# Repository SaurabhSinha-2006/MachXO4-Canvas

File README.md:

# MachXO4-Canvas

**MachXO4-Canvas** is a flexible, beginner-friendly FPGA development board designed specifically for educational use and DIY assembly. Built on a standard 100x100mm 2-layer PCB, this board eliminates standard manufacturing and assembly bottlenecks by utilizing robust, easy-to-solder components, including a massive through-hole USB-A female connector. 

With zero Design Rule Check (DRC) errors, this layout is highly optimized for standard 2-layer board house constraints.

## Repository Structure

Based on the project organization, here is where to find all relevant design and production files:

*   **[`/Doc`](Doc/)**[cite: 3]
    *   [`machx04_devboard.png`](Doc/machx04_devboard.png) - High-resolution 3D render of the final board[cite: 3].
    *   [`machx04_devboard.pdf`](Doc/machx04_devboard.pdf) - The complete system schematic[cite: 3].
    *   [`layout_final.pdf`](Doc/layout_final.pdf) - High-resolution 2D PCB layout for visual routing inspection[cite: 3].
*   **[`/Fabrication`](Fabrication/)**[cite: 3]
    *   [`machx04_gerber_files.zip`](Fabrication/machx04_gerber_files.zip) - The final, production-ready Gerber and Drill files[cite: 3].
*   **[`/Hardware`](Hardware/)**[cite: 3]
    *   Contains the native KiCad 8 source files (`.kicad_pro`, `.kicad_sch`, `.kicad_pcb`) and the `/Custom Library` folder for component footprints and symbols[cite: 3].

## Hardware Specifications

*   **Core Processor:** MachXO4 FPGA paired with a dedicated configuration EEPROM.
*   **Programming Interface:** Onboard FTDI JTAG/UART bridge for seamless flashing and serial communication directly over USB.
*   **Power Architecture:** 5V to 3.3V and 1.8V low-dropout (LDO) regulators with optimized thermal copper pours.
*   **User I/O:** Programmable onboard LEDs, tactile user switches, and a dedicated hardware system reset.
*   **Form Factor & Connectivity:** 100x100mm Edge.Cuts with a robust, 4-pin female USB-A interface, entirely removing the microscopic drill constraints of standard USB-C ports.

## Fabrication & Manufacturing

This board is fully validated for standard, low-cost 2-layer manufacturing. 
To manufacture this board, simply provide the factory with the **[Gerber Release ZIP](Fabrication/machx04_gerber_files.zip)**[cite: 3]. 

If your fabrication engineer requires a visual preview before running the job, you can share the **[2D Layout PDF](Doc/layout_final.pdf)**[cite: 3] and the **[System Schematic](Doc/machx04_devboard.pdf)**[cite: 3].

## Modifying the Design

To open and modify this project:
1. Clone this repository to your local machine.
2. Ensure you have KiCad installed.
3. Navigate to the `Hardware/` directory and open `machx04_devboard.kicad_pro`[cite: 3].
4. The project utilizes localized parts in the `Hardware/Custom Library/` folder, which should link automatically upon opening[cite: 3].

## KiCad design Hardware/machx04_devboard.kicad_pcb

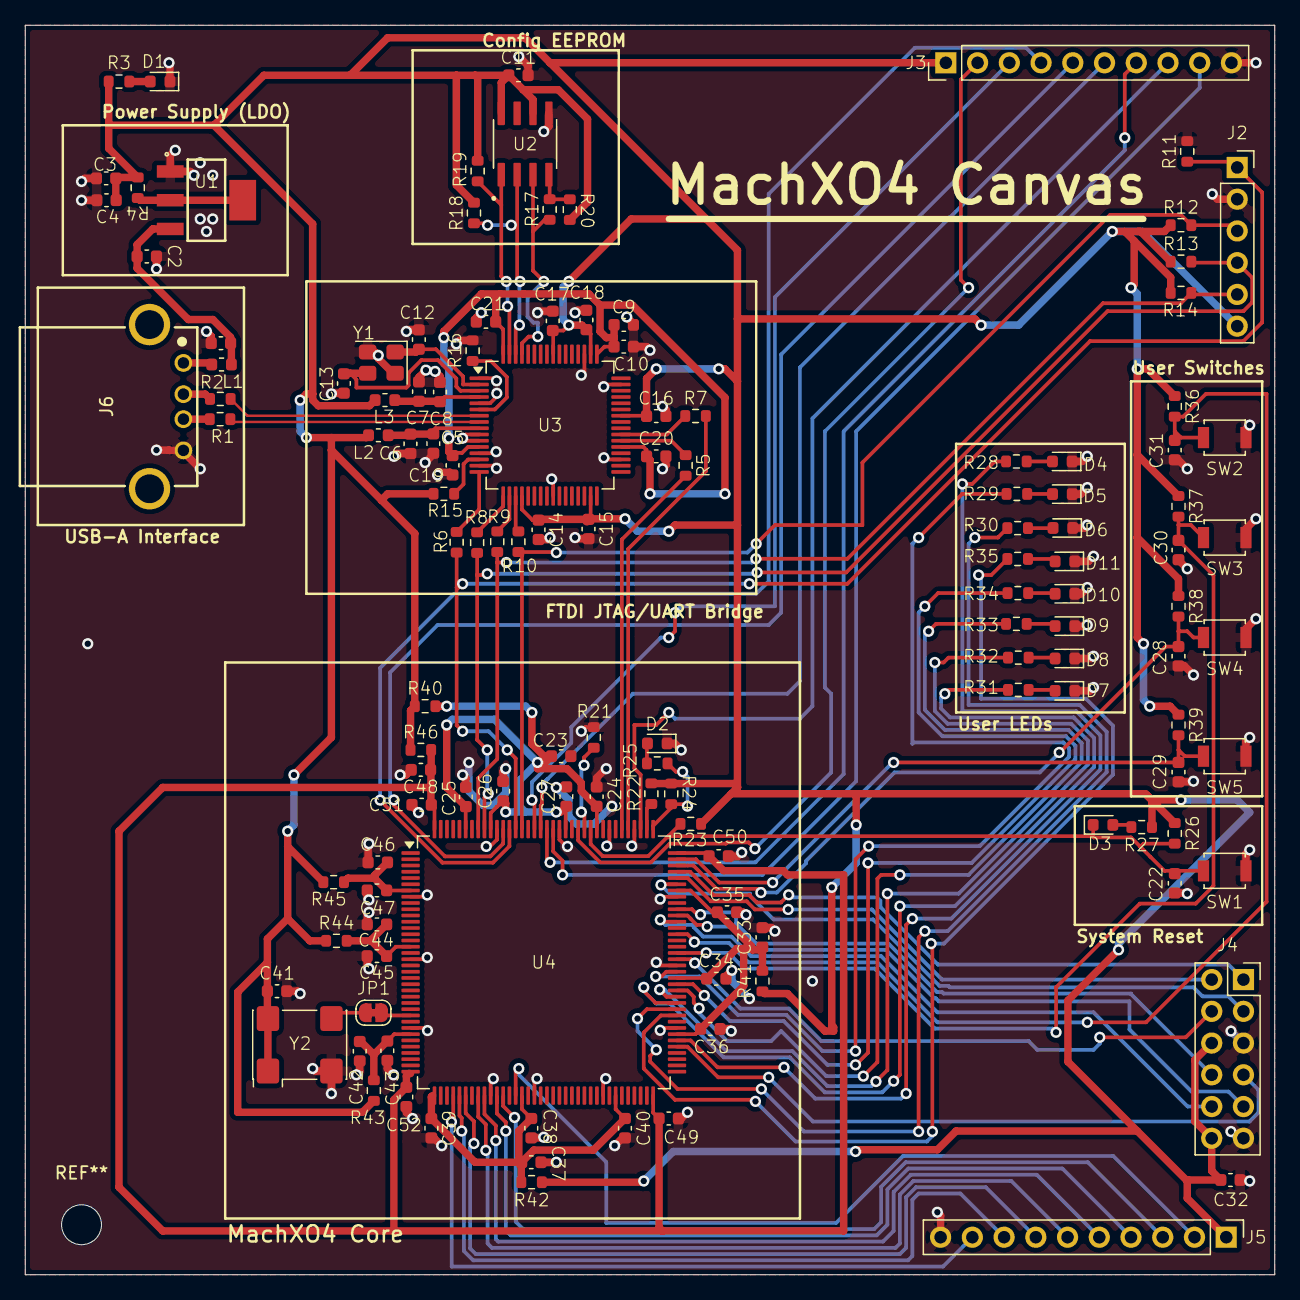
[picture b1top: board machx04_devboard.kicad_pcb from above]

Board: 2 copper layers, 100.0 x 100.0 mm, 129 parts (0 on the bottom side), 92 nets.

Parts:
C1, C4, C5, C8, C10, C11, C14, C15, C16, C17, C18, C19, C20, C21, C22, C24, C25, C26, C27, C28, C29, C30, C31, C32, C34, C35, C36, C38, C39, C40, C41, C43, C45, C47, C49, C50, C51, C52: 0.1uf; C_0603_1608Metric
C2, C9, C23, C33, C37, C42, C44, C46, C48: 10uf; C_0603_1608Metric
C3: 22uf; C_0603_1608Metric
C6, C7: 4.7uf; C_0603_1608Metric
C12, C13: 18pf; C_0603_1608Metric
D1, D2, D3, D4, D5, D6, D7, D8, D9, D10, D11: LED; LED_0603_1608Metric
J2: Conn_01x06_Socket; PinSocket_1x06_P2.54mm_Vertical
J3, J5: Conn_01x10_Socket; PinHeader_1x10_P2.54mm_Vertical
J4: Conn_02x06_Top_Bottom; PinSocket_2x06_P2.54mm_Vertical
J6: USB_A; 61400416021
JP1: Jumper_2_Open; SolderJumper-2_P1.3mm_Bridged_RoundedPad1.0x1.5mm
L1, L2, L3: 600ohm 500mA; L_0603_1608Metric
R1, R2, R4, R5, R6, R7, R8, R9, R10: 0; R_0603_1608Metric
R3, R25, R27, R28, R29, R30, R31, R32, R33, R34, R35: 1k; R_0603_1608Metric
R11, R15, R17: 2.2k; R_0603_1608Metric
R12, R13, R14, R26, R36, R37, R38, R39: 4.7k; R_0603_1608Metric
R16: 12k; R_0603_1608Metric
R18, R19, R20, R21, R22, R23, R24: 10k; R_0603_1608Metric
R40, R41, R42, R43, R44, R45, R46: 1; R_0603_1608Metric
SW1, SW2, SW3, SW4, SW5: SW_Push; SW_SPST_B3U-1000P
U1: NCP1117ST33T3G; SOT230P700X180-4N
U2: 93LC56C-I_SN; SOIC127P600X175-8N
U3: FT2232HL; LQFP-64_10x10mm_P0.5mm
U4: MachXO4_TQFP144; TQFP-144_20x20mm_P0.5mm
Y1: Crystal_GND24; Crystal_SMD_3225-4Pin_3.2x2.5mm
Y2: SG-8002CA; Oscillator_SMD_SeikoEpson_SG8002CA-4Pin_7.0x5.0mm

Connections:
+3.3V: C3.1, C4.1, C11.1, C14.1, C15.1, C16.1, C17.1, C18.1, C32.1, C41.1, J2.6, J3.1, J4.6, J4.12, J5.1, L2.1, L3.1, R3.1, R4.2, R12.1, R13.1, R14.1, R15.1, R18.1, R19.1, R20.1, R22.1, R23.1, R24.1, R26.1, R27.1, R36.1, R37.1, R38.1, R39.1, R40.1, R41.1, R42.1, R43.1, R44.1, R45.1, R46.1, U2.6 (ORG), U2.8 (VCC), U3.20 (VCCIO), U3.31 (VCCIO), U3.42 (VCCIO), U3.50 (VREGIN), U3.56 (VCCIO), Y2.1 (OE), Y2.4 (Vcc)
/bank0/EXP_HEADER1: J3.2, U4.121 (PT21B)
/bank0/EXP_HEADER2: J3.3, U4.128 (PT18A)
/bank0/EXP_HEADER3: J3.4, U4.132 (PT14B)
/bank0/EXP_HEADER4: J3.5, U4.133 (PT14A)
/bank0/EXP_HEADER5: J3.6, U4.127 (PT18B)
/bank0/EXP_HEADER6: J3.7, U4.126 (PT20C)
/bank0/EXP_HEADER7: J3.8, U4.111 (PT27B)
/bank0/EXP_HEADER8: J3.9, U4.125 (PT20D)
/bank1/LED1: R28.1, U4.78 (PR16A)
/bank1/LED2: R29.1, U4.89 (PR10C)
/bank1/LED3: R30.1, U4.83 (PR14B)
/bank1/LED4: R31.1, U4.84 (PR14A)
/bank1/LED5: R32.1, U4.85 (PR13B)
/bank1/LED6: R33.1, U4.86 (PR13A)
/bank1/LED7: R34.1, U4.87 (PR10D)
/bank1/LED8: R35.1, U4.82 (PR15A)
/bank1/PB1: C31.1, R36.2, SW2.2, U4.95 (PR8B)
/bank1/PB2: C30.1, R37.2, SW3.2, U4.92 (PR10A)
/bank1/PB3: C29.1, R39.2, SW5.2, U4.107 (PR2A)
/bank1/PB4: C28.1, R38.2, SW4.2, U4.106 (PR2B)
/bank1/PM1: J4.1, U4.105 (PR3A)
/bank1/PM2: J4.2, U4.104 (PR3B)
/bank1/PM3: J4.3, U4.103 (PR4C)
/bank1/PM4: J4.4, U4.91 (PR10B)
/bank1/PM5: J4.7, U4.77 (PR16B)
/bank1/PM6: J4.8, U4.99 (PR5B)
/bank1/PM7: J4.9, U4.98 (PR6A)
/bank1/PM8: J4.10, U4.97 (PR6B)
/bank2/EXP_HEAD9: J5.2, U4.50 (PB13B)
/bank2/EXP_HEAD10: J5.3, U4.48 (PB10B)
/bank2/EXP_HEAD11: J5.4, U4.47 (PB10A)
/bank2/EXP_HEAD12: J5.5, U4.45 (PB9B)
/bank2/EXP_HEAD13: J5.6, U4.44 (PB9A)
/bank2/EXP_HEAD14: J5.7, U4.42 (PB7A)
/bank2/EXP_HEAD15: J5.8, U4.41 (PB4B)
/bank2/EXP_HEAD16: J5.9, U4.40 (PB4A)
GND: C1.2, C2.2, C3.2, C4.2, C5.2, C6.2, C7.2, C8.2, C9.2, C10.2, C11.2, C12.2, C13.2, C14.2, C15.2, C16.2, C17.2, C18.2, C19.2, C20.2, C21.2, C22.2, C23.2, C24.2, C25.2, C26.2, C27.2, C28.2, C29.2, C30.2, C31.2, C32.2, C33.2, C34.2, C35.2, C36.2, C37.2, C38.2, C39.2, C40.2, C41.2, C42.1, C43.1, C44.1, C45.1, C46.1, C47.1, C48.2, C49.2, C50.2, C51.2, C52.2, D1.1 (K), D2.1 (K), D4.1 (K), D5.1 (K), D6.1 (K), D7.1 (K), D8.1 (K), D9.1 (K), D10.1 (K), D11.1 (K), J2.2, J3.10, J4.5, J4.11, J5.10, J6.4 (GND), R11.2, R16.1, R21.2, SW1.1, SW2.1, SW3.1, SW4.1, SW5.1, U1.1 (GND), U2.5 (VSS), U3.1 (GND), U3.5 (GND), U3.10 (AGND), U3.11 (GND), U3.13 (TEST), U3.15 (GND), U3.25 (GND), U3.35 (GND), U3.47 (GND), U3.51 (GND), U4.8 (GND), U4.18 (GND), U4.29 (GND), U4.46 (GND), U4.53 (GND), U4.64 (GND), U4.80 (GND), U4.90 (GND), U4.101 (GND), U4.112 (GND), U4.116 (GND), U4.124 (GND), U4.134 (GND), Y1.2 (G), Y1.4 (G), Y2.2 (GND)
unnamed: D1.2 (A), R3.2
unnamed: D2.2 (A), R25.2
unnamed: D3.2 (A), R27.2
unnamed: D4.2 (A), R28.2
unnamed: D5.2 (A), R29.2
unnamed: D6.2 (A), R30.2
unnamed: D7.2 (A), R31.2
unnamed: D8.2 (A), R32.2
unnamed: D9.2 (A), R33.2
unnamed: D10.2 (A), R34.2
unnamed: D11.2 (A), R35.2
unnamed: J6.3 (D+), R1.1
unnamed: J6.2 (D-), R2.1
unnamed: J6.1 (VBUS), L1.2
unnamed: JP1.1 (A), U4.27 (PL17A)
unnamed: JP1.2 (B), Y2.3 (OUT)
unnamed: R4.1, U1.2 (OUT), U1.4 (OUT)
unnamed: R18.2, U2.2 (CLK), U3.62 (EECLK)
unnamed: R19.2, U2.1 (CS), U3.63 (EECS)
unnamed: R17.2, U2.3 (DI), U3.61 (EEDATA)
unnamed: R17.1, R20.2, U2.4 (DO)
unnamed: R6.1, U3.16 (ADBUS0)
unnamed: R8.1, U3.17 (ADBUS1)
unnamed: R9.1, U3.18 (ADBUS2)
unnamed: R10.1, U3.19 (ADBUS3)
unnamed: R5.1, U3.38 (BDBUS0)
unnamed: R7.1, U3.39 (BDBUS1)
unnamed: C12.1, U3.2 (OSCI), Y1.1
unnamed: C13.1, U3.3 (OSCO), Y1.3
unnamed: R16.2, U3.6 (REF)
unnamed: C7.1, C8.1, L3.2, U3.4 (VPHY)
unnamed: C5.1, C6.1, L2.2, U3.9 (VPLL)
unnamed: R15.2, U3.14 (~RESET)
unnamed: R21.1, U4.120 (PT23C)
unnamed: R22.2, U4.110 (PT28C)
unnamed: R24.2, R25.1, U4.109 (PT28D)
PROGRAMN: C22.1, D3.1 (K), R23.2, R26.2, SW1.2, U4.119 (PT23D)
Rx: R5.2, U4.114 (PT25A)
TCK: J2.1, R6.2, R11.1, U4.131 (PT15C)
TDI: J2.4, R8.2, R13.2, U4.136 (PT13D)
TDO: J2.5, R9.2, R14.2, U4.137 (PT13C)
TMS: J2.3, R10.2, R12.2, U4.130 (PT15D)
Tx: R7.2, U4.113 (PT25B)
USB_D+: R1.2, U3.8 (DP)
USB_D-: R2.2, U3.7 (DM)
VCC1_8FT: C9.1, C10.1, C19.1, C20.1, C21.1, U3.12 (VCORE), U3.37 (VCORE), U3.49 (VREGOUT), U3.64 (VCORE)
VCCIO0: C23.1, C24.1, C25.1, C26.1, C27.1, R40.2, U4.118 (VCCIO0), U4.123 (VCCIO0), U4.135 (VCCIO0), U4.139 (VCCIO0)
VCCIO1: C33.1, C34.1, C35.1, C36.1, R41.2, U4.79 (VCCIO1), U4.88 (VCCIO1), U4.102 (VCCIO1)
VCCIO2: C37.1, C38.1, C39.1, C40.1, R42.2, U4.37 (VCCIO2), U4.51 (VCCIO2), U4.66 (VCCIO2)
VCCIO3: C42.2, C43.2, R43.2, U4.30 (VCCIO3)
VCCIO4: C44.2, C45.2, R44.2, U4.16 (VCCIO4)
VCCIO5: C46.2, C47.2, R45.2, U4.7 (VCCIO5)
VCC_CORE: C48.1, C49.1, C50.1, C51.1, C52.1, R46.2, U4.36 (VCC), U4.72 (VCC), U4.108 (VCC), U4.144 (VCC)
Vbus_+5V: C1.1, C2.1, L1.1, U1.3 (IN)
